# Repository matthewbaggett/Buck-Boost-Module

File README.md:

# Buck-Boost-Module
Small 0.75" square PCB with a buck/boost module pair, based on the Adafruit Powerboost 1000

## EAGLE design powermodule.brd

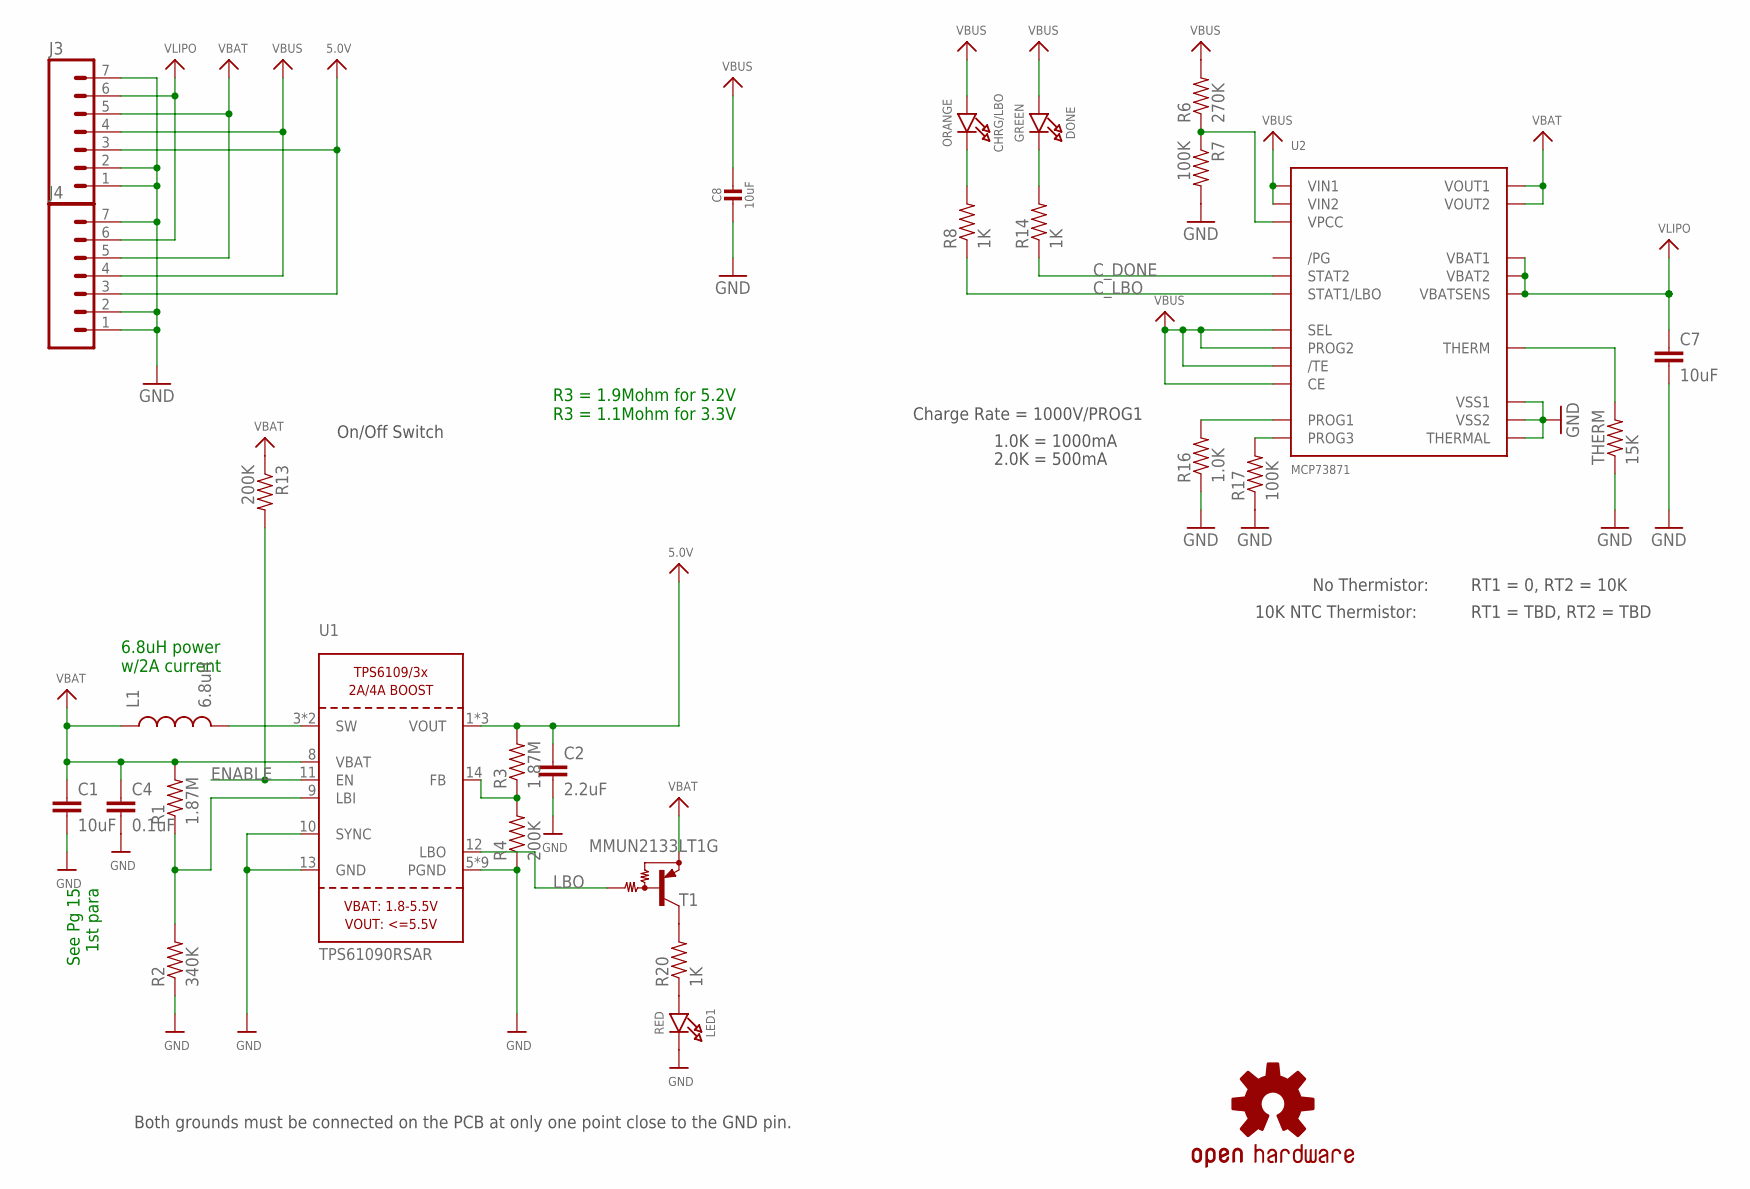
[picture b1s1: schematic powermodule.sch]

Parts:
C1, C7: 10uF; 0603-CAP
C2: 2.2uF; 0603-CAP
C4: 0.1uF; 0603-CAP
C8: 10uF; 0805-NO
CHRG/LBO: ORANGE; CHIPLED_0805_NOOUTLINE
DONE: GREEN; CHIPLED_0805_NOOUTLINE
J3, J4: M07; 1X07
L1: 6.8uH; SRU5028
LED1: RED; CHIPLED_0805_NOOUTLINE
LOGO1: OSHW-LOGOS; OSHW-LOGO-S
R1, R3: 1.87M; 0603-RES
R2: 340K; 0603-RES
R4, R13: 200K; 0603-RES
R6: 270K; 0603-RES
R7, R17: 100K; 0603-RES
R8, R14, R20: 1K; 0603-RES
R16: 1.0K; 0603-RES
T1: MMUN2133LT1G; SC59-BEC
THERM: 15K; 0603-RES
U1: TPS61090RSAR; PVQFN-16
U2: MCP73871; QFN20_4MM

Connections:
5.0V: C2.1, J3.3, J4.3, R3.2, U1.1 (VOUT), U1.15 (VOUT), U1.16 (VOUT)
C_DONE: R14.1, U2.P$7 (STAT2)
C_LBO: R8.1, U2.P$8 (STAT1/LBO)
ENABLE: R13.2, U1.11 (EN)
GND: C1.2, C2.2, C4.2, C7.2, C8.2, J3.1, J3.2, J3.7, J4.1, J4.2, J4.7, LED1.C, R2.1, R4.1, R7.2, R16.1, R17.1, THERM.1, U1.5 (PGND), U1.6 (PGND), U1.7 (PGND), U1.10 (SYNC), U1.13 (GND), U1.P$18 (PGND), U1.P$19 (PGND), U1.P$20 (PGND), U1.P$21 (PGND), U1.P$22 (PGND), U1.THERMAL (PGND), U2.P$10 (VSS1), U2.P$11 (VSS2), U2.P$21 (THERMAL)
LBO: T1.B, U1.12 (LBO)
unnamed: L1.2, U1.3 (SW), U1.4 (SW)
unnamed: LED1.A, R20.1
unnamed: R1.1, R2.2, U1.9 (LBI)
unnamed: R3.1, R4.2, U1.14 (FB)
unnamed: R20.2, T1.C
unnamed: R6.1, R7.1, U2.P$2 (VPCC)
unnamed: DONE.C, R14.2
unnamed: THERM.2, U2.P$5 (THERM)
unnamed: CHRG/LBO.C, R8.2
unnamed: R17.2, U2.P$12 (PROG3)
unnamed: R16.2, U2.P$13 (PROG1)
VBAT: C1.1, C4.1, J3.5, J4.5, L1.1, R1.2, R13.1, T1.E, U1.8 (VBAT), U2.P$1 (VOUT1), U2.P$20 (VOUT2)
VBUS: C8.1, CHRG/LBO.A, DONE.A, J3.4, J4.4, R6.2, U2.P$3 (SEL), U2.P$4 (PROG2), U2.P$9 (/TE), U2.P$17 (CE), U2.P$18 (VIN1), U2.P$19 (VIN2)
VLIPO: C7.1, J3.6, J4.6, U2.P$14 (VBAT1), U2.P$15 (VBAT2), U2.P$16 (VBATSENS)

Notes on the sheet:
Both grounds must be connected on the PCB at only one point close to the GND pin.
On/Off Switch
See Pg 15 1st para
6.8uH power w/2A current
R3 = 1.9Mohm for 5.2V R3 = 1.1Mohm for 3.3V
Charge Rate = 1000V/PROG1
1.0K = 1000mA
2.0K = 500mA
No Thermistor:
10K NTC Thermistor:
RT1 = 0, RT2 = 10K
RT1 = TBD, RT2 = TBD

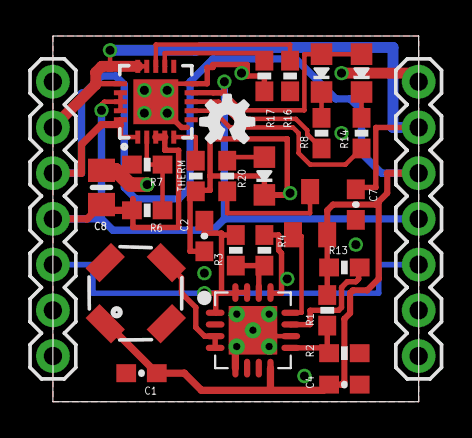
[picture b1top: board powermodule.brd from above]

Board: 2 copper layers, 20.3 x 20.3 mm, 28 parts (0 on the bottom side), 20 nets.

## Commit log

2016-12-03 Initial version
2016-12-03 Slight layout change to remove some 90 degree bends
2016-12-04 Slight improvement to ground coverage
2016-12-04 Made board slightly wider so it fits into a breadboard right.

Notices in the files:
parts and their libraries:
microbuilder: This work is placed in the public domain, and may be freely used for commercial and non-commercial work with the following conditions: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
SparkFun-Connectors: Licensing: Creative Commons ShareAlike 4.0 International - https://creativecommons.org/licenses/by-sa/4.0
